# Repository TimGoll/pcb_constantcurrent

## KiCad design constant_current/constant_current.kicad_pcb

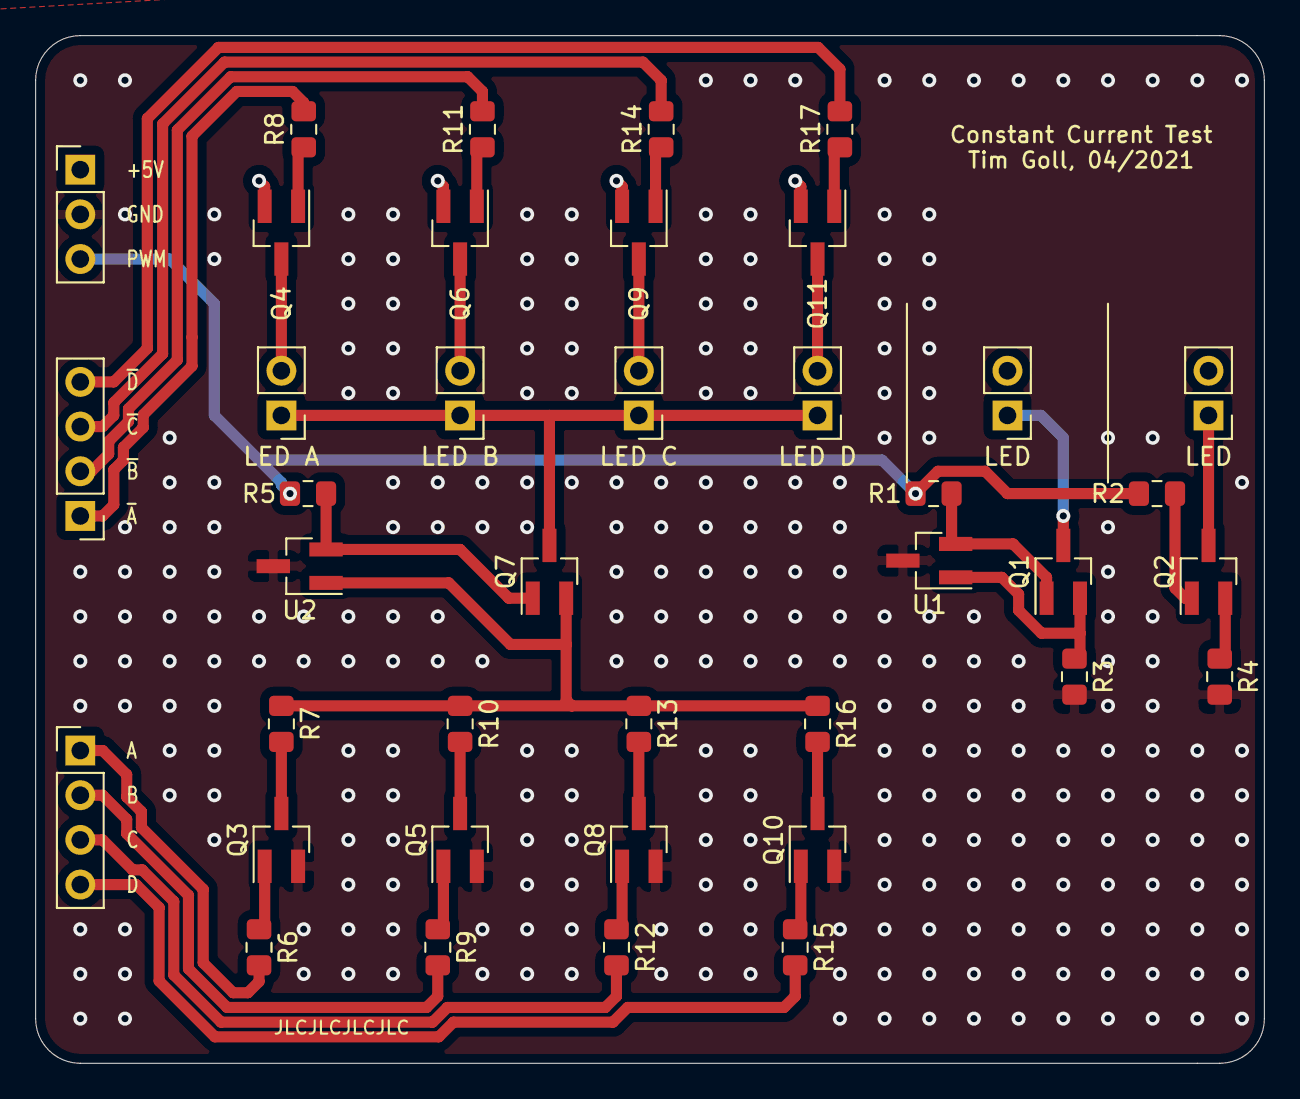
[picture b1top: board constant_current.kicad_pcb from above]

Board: 2 copper layers, 69.9 x 58.4 mm, 39 parts (0 on the bottom side), 36 nets.

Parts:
J1: conn_in; PinHeader_1x03_P2.54mm_Vertical
J4: ~enb; PinHeader_1x04_P2.54mm_Vertical
J5: enb; PinHeader_1x04_P2.54mm_Vertical
LED: LED; PinHeader_1x02_P2.54mm_Vertical
LED A: LED_A; PinHeader_1x02_P2.54mm_Vertical
LED B: LED_B; PinHeader_1x02_P2.54mm_Vertical
LED C: LED_C; PinHeader_1x02_P2.54mm_Vertical
LED D: LED_D; PinHeader_1x02_P2.54mm_Vertical
LED#2: LED_R; PinHeader_1x02_P2.54mm_Vertical
Q1, Q2, Q3, Q5, Q7, Q8, Q10: BC847C; SOT-23_Handsoldering
Q4, Q6, Q9, Q11: BC857C; SOT-23_Handsoldering
R1, R2, R5, R6, R8, R9, R11, R12, R14, R15, R17: 1k; R_0805_2012Metric_Pad1.15x1.40mm_HandSolder
R3, R7, R10, R13, R16: 62R; R_0805_2012Metric_Pad1.15x1.40mm_HandSolder
R4: 150R; R_0805_2012Metric_Pad1.15x1.40mm_HandSolder
U1, U2: tlv431; SOT-23_Handsoldering

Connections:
+5V: J1.1, LED.2, LED#2.2, Q4.2, Q6.2, Q9.2, Q11.2
A: J5.1, R6.2
B: J5.2, R9.2
C: J5.3, R12.2
D: J5.4, R15.2
GND: J1.2, Q3.2, Q5.2, Q8.2, Q10.2, R3.2, R4.2, U1.3, U2.3
unnamed: LED.1, Q1.3
unnamed: LED#2.1, Q2.3
unnamed: LED A.1, LED B.1, LED C.1, LED D.1, Q7.3
unnamed: LED A.2, Q4.3
unnamed: LED B.2, Q6.3
unnamed: LED C.2, Q9.3
unnamed: LED D.2, Q11.3
unnamed: Q1.1, R1.2, U1.2
unnamed: Q1.2, R3.1, U1.1
unnamed: Q2.1, R2.2
unnamed: Q2.2, R4.1
unnamed: Q3.1, R6.1
unnamed: Q3.3, R7.2
unnamed: Q4.1, R8.1
unnamed: Q5.1, R9.1
unnamed: Q5.3, R10.2
unnamed: Q6.1, R11.1
unnamed: Q7.1, R5.2, U2.2
unnamed: Q7.2, R7.1, R10.1, R13.1, R16.1, U2.1
unnamed: Q8.1, R12.1
unnamed: Q8.3, R13.2
unnamed: Q9.1, R14.1
unnamed: Q10.1, R15.1
unnamed: Q10.3, R16.2
unnamed: Q11.1, R17.1
pwm: J1.3, R1.1, R2.1, R5.1
~A: J4.1, R8.2
~B: J4.2, R11.2
~C: J4.3, R14.2
~D: J4.4, R17.2

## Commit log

2021-04-13 finished pcb
